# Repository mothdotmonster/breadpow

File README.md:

# breadpow
USB PD breadboard doodad

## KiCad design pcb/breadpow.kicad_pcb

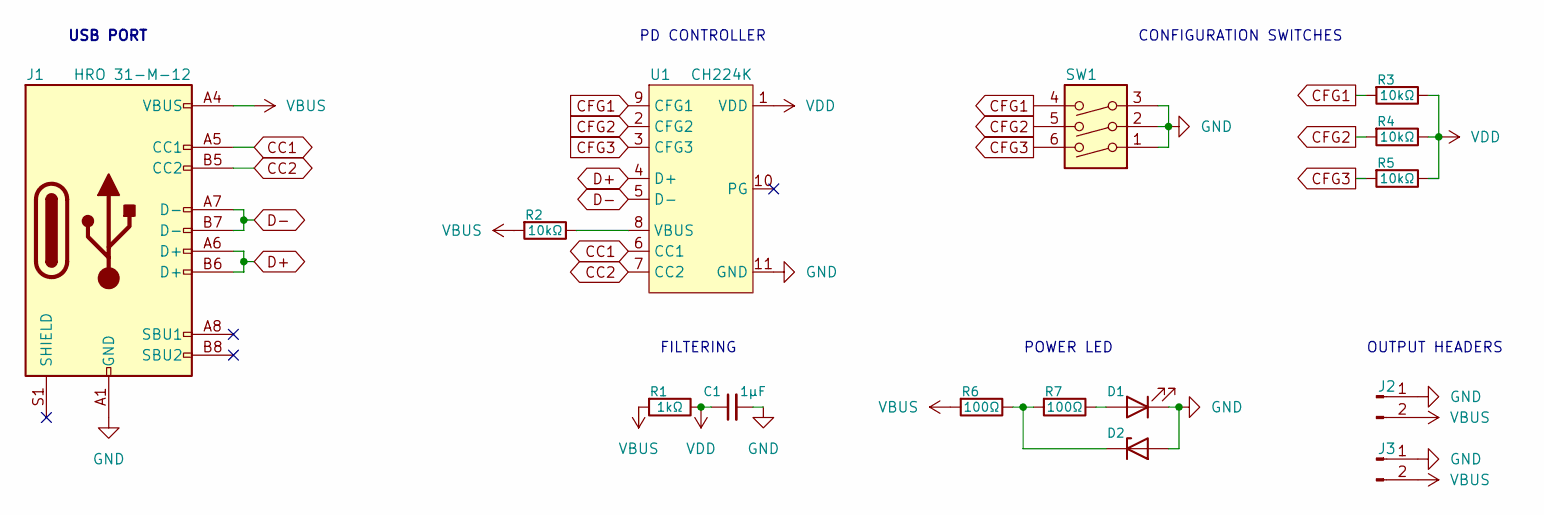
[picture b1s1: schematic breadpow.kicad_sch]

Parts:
C1: 1µF; C_0603_1608Metric; JLC C15849
D1: LED; LED_0603_1608Metric; JLC C2286
D2: D_Zener; D_MiniMELF; JLC C2857251
J1: HRO 31-M-12; USB_C_Receptacle_HRO_TYPE-C-31-M-12; JLC C165948
J2, J3: Conn_01x02_Pin; PinHeader_1x02_P2.54mm_Vertical
R1: 1kΩ; R_0603_1608Metric; JLC C21190
R2, R3, R4, R5: 10kΩ; R_0603_1608Metric; JLC C25804
R6, R7: 100Ω; R_0603_1608Metric; JLC C22775
SW1: SW_DIP_x03; DSHP03TSGER; JLC C3293143
U1: CH224K; CH224K_ESSOP10; JLC C970725

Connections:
CC1: J1.A5 (CC1), U1.6 (CC1)
CC2: J1.B5 (CC2), U1.7 (CC2)
CFG1: R3.2, SW1.4, U1.9 (CFG1)
CFG2: R4.2, SW1.5, U1.2 (CFG2)
CFG3: R5.2, SW1.6, U1.3 (CFG3)
D+: J1.A6 (D+), J1.B6 (D+), U1.4 (D+)
D-: J1.A7 (D-), J1.B7 (D-), U1.5 (D-)
GND: C1.2, D1.1 (K), D2.2 (A), J1.A1 (GND), J1.A12 (GND), J1.B1 (GND), J1.B12 (GND), J2.1, J3.1, SW1.1, SW1.2, SW1.3, U1.11 (GND)
unnamed: D1.2 (A), R7.1
unnamed: D2.1 (K), R6.1, R7.2
unnamed: R2.1, U1.8 (VBUS)
VBUS: J1.A4 (VBUS), J1.A9 (VBUS), J1.B4 (VBUS), J1.B9 (VBUS), J2.2, J3.2, R1.2, R2.2, R6.2
VDD: C1.1, R1.1, R3.1, R4.1, R5.1, U1.1 (VDD)

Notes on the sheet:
PD CONTROLLER
USB PORT
CONFIGURATION SWITCHES
FILTERING
OUTPUT HEADERS
POWER LED

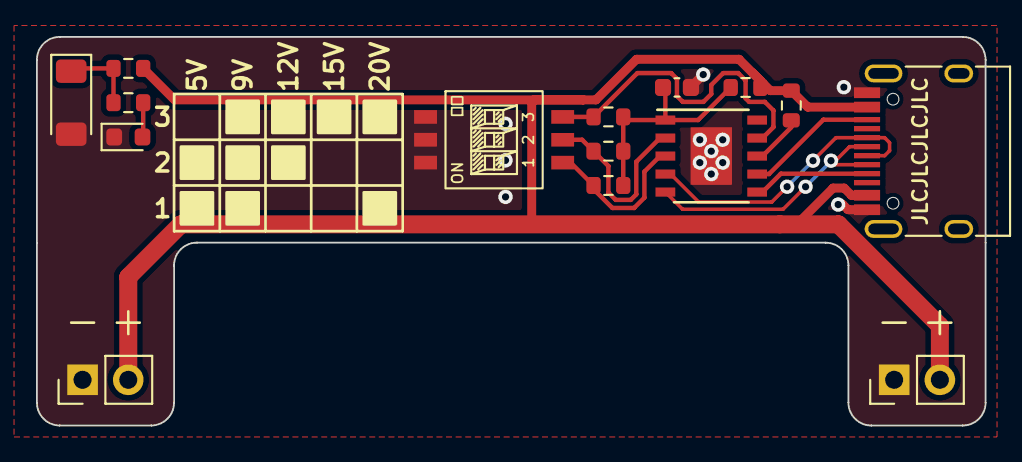
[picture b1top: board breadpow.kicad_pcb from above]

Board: 2 copper layers, 52.7 x 21.6 mm, 15 parts (0 on the bottom side), 13 nets.

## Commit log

2023-08-18 add license
2023-08-18 add v0.1.1 pcb
2023-08-18 forgot to add that
2023-08-31 0.1.2 fixes dimensions

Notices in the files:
pcb/breadpow.kicad_pcb:
CC-BY
